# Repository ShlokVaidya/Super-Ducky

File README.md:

# Super-Ducky
# RP2350A Dual-Mode USB Device

## 1. Description

This project is a custom USB storage and control device powered by the **Raspberry Pi RP2350A** microcontroller. It serves as a dualmode device separating system firmware from user data through a high-speed eMMC interface

The system architecture utilizes a 4-layer PCB to maintain signal integrity for high-speed digital lines (USB and eMMC).

| Component | Function |
| :---- | :---- |
| **RP2350A** | Central MCU handling USB stack and storage logic |
| **eMMC (16GB)** | High density mass storage for user data |
| **QSPI Flash** | Dedicated firmware and bootloader execution |
| **LDO Regulators** | AP2112K series for stable 1.8V and 3.3V rails |
| **USB Mux** | TS3USB221 for signal routing and integrity |

## 2. Why I Built This

I built this project to explore **full stack embedded system development**.

Most beginner projects focus only on firmware or simple microcontroller boards. This project instead focuses on the **entire engineering process** including:

- **Hardware Architecture:** Designing a system that separates firmware execution (QSPI) from high-capacity storage (eMMC).
- **Advanced Sourcing:** Navigating global supply chains to source specialized ICs like the MTFC16GAKAEDQ-AIT eMMC via JLCPCB Global Sourcing.
- **High-Speed Design:** Learning to route differential USB pairs and high-clock-rate storage interfaces on a multi-layer board.
- **Power Management:** Implementing a multi-rail (3.3V/1.8V) system to satisfy different logic level requirements.

The goal was to move beyond hobbyist "breadboarding" and understand how professional-grade embedded products are engineered from the ground up.

## 3. How to Use the Device

1. **Connection:** Connect the device to a computer using a standard USB-C cable.
2. **Standard Operation:** The RP2350A initializes, loads firmware from the QSPI flash, and mounts the eMMC as a storage drive or serial device depending on the firmware configuration.
3. **Boot Selection:** To update firmware or change modes, hold the **Boot Button (GPIO22)** while plugging in the device. This forces the RP2350A into its native USB bootloader mode.
4. **Data Access:** Once connected, the host computer interacts with the 16GB eMMC through the high-speed USB interface managed by the MCU.

## 4. Hardware Visualization

### Full Schematic

### PCB Layout

### 3D Render

### BOM

## 5. Bill of Materials (BOM)

The following table lists all 20 parts required for the assembly, consolidated from the design files and JLCPCB procurement logs.

| Parts Type | JLCPCB Part \# | MFR Part \# | Link | Description | Unit Price | Qty | Total Price |
| :---- | :---- | :---- | :---- | :---- | :---- | :---- | :---- |
| stock | C1711 | CL21B104KBCNNNC | https://jlcpcb.com/partdetail/2063-CL21B104KBCNNNC/C1711 | 100nF 50V X7R ±10% 0805 Multilayer Ceramic Capacitors MLCC \- SMD/SMT ROHS | 0.0062 | 16 | 0.1 |
| stock | C8429 | WJ2EDGV-5.08-04P-14-00A | https://jlcpcb.com/partdetail/8923-WJ2EDGV\_5\_08\_04P\_1400A/C8429 | \-40℃\~+105℃ 1 10A 1x4P 300V 4 4P 5.08mm Board Side/Socket \- Open Green Hinged (Snap On) Through Hole Plugin,P=5.08mm Pluggable System Terminal Block ROHS | 0.0905 | 2 | 0.19 |
| stock | C1779 | CL21A475KAQNNNE | https://jlcpcb.com/partdetail/2131-CL21A475KAQNNNE/C1779 | 25V 4.7uF X5R ±10% 0805 Multilayer Ceramic Capacitors MLCC \- SMD/SMT ROHS | 0.0143 | 2 | 0.03 |
| buy | C6006988 | UP31-CV-G-CM | https://jlcpcb.com/partdetail/CUI-UP31\_CV\_GCM/C6006988 | \- USB Connectors ROHS | 2.265 | 4 | 9.06 |
| stock | C71617 | CRCW040210K0FKED | https://jlcpcb.com/partdetail/VishayIntertech-CRCW040210K0FKED/C71617 | \-55℃\~+155℃ 10kΩ 50V 63mW Thick Film Resistor ±1% ±100ppm/℃ 0402 Chip Resistor \- Surface Mount ROHS | 0.0035 | 6 | 0.03 |
| buy | C100612 | CR0402JF0220G | https://jlcpcb.com/partdetail/LIZElec-CR0402JF0220G/C100612 | \-55℃\~+125℃ 22Ω 50V 62.5mW Thick Film Resistor ±200ppm/℃ ±5% 0402 Chip Resistor \- Surface Mount ROHS | 0.0003 | 10000 | 3 |
| stock | C25905 | 0402WGF5101TCE | https://jlcpcb.com/partdetail/26648-0402WGF5101TCE/C25905 | \-55℃\~+155℃ 5.1kΩ 50V 62.5mW Thick Film Resistor ±1% ±100ppm/℃ 0402 Chip Resistor \- Surface Mount ROHS | 0.0008 | 4 | 0.01 |
| stock | C25792 | 0402WGF4702TCE | https://jlcpcb.com/partdetail/26535-0402WGF4702TCE/C25792 | \-55℃\~+155℃ 47kΩ 50V 62.5mW Thick Film Resistor ±1% ±100ppm/℃ 0402 Chip Resistor \- Surface Mount ROHS | 0.0008 | 10 | 0.01 |
| stock | C25530 | 0402WGJ0104TCE | https://jlcpcb.com/partdetail/26273-0402WGJ0104TCE/C25530 | \-55℃\~+155℃ 100kΩ 50V 62.5mW Thick Film Resistor ±100ppm/℃ ±5% 0402 Chip Resistor \- Surface Mount ROHS | 0.0006 | 4 | 0.01 |
| stock | C25076 | 0402WGF1000TCE | https://jlcpcb.com/partdetail/25819-0402WGF1000TCE/C25076 | \-55℃\~+155℃ 100Ω 50V 62.5mW Thick Film Resistor ±1% ±100ppm/℃ 0402 Chip Resistor \- Surface Mount ROHS | 0.0008 | 2 | 0.01 |
| stock | C1712 | CL21B105KAFNFNE | https://jlcpcb.com/partdetail/2064-CL21B105KAFNFNE/C1712 | 1uF 25V X7R ±10% 0805 Multilayer Ceramic Capacitors MLCC \- SMD/SMT ROHS | 0.0133 | 18 | 0.24 |
| stock | C138714 | TPD4E05U06DQAR | https://jlcpcb.com/partdetail/TexasInstruments-TPD4E05U06DQAR/C138714 | \-40℃\~+125℃ 0.5pF 10nA 14V 2.5A@8/20us 4 40W@8/20us 5.5V 6.5V ESD IEC 61000-4-2、IEC 61000-4-5、IEC 61000-4-4 Unidirectional USON-10(1x2.5) ESD and Surge Protection (TVS/ESD) ROHS | 0.072 | 2 | 0.15 |
| stock | C295091 | XJHCELNANF-12MHZ | https://jlcpcb.com/partdetail/TAITIENElec-XJHCELNANF12MHZ/C295091 | \-40℃\~+85℃ 12MHz 20pF Crystal Oscillator ±30ppm ±30ppm HC-49S-SMD Crystals ROHS | 0.1385 | 2 | 0.28 |
| stock | C176944 | AP2112K-1.8TRG1 | https://jlcpcb.com/partdetail/DiodesIncorporated-AP2112K\_18TRG1/C176944 | \-40℃\~+85℃@(Ta) 1 1.8V 500mV@(600mA) 50uVrms 55uA 600mA 65dB@(1kHz) 6V Fixed Over Current Protection、Over Temperature Protection、Enable Positive SOT-25 Voltage Regulators \- Linear, Low Drop Out (LDO) Regulators ROHS | 0.1103 | 2 | 0.23 |
| stock | C128396 | TS3USB221ARSER | https://jlcpcb.com/partdetail/TexasInstruments-TS3USB221ARSER/C128396 | \-40℃\~+85℃ 12ns 2.3V\~3.6V 250ps 2:1 30ns 6pF 6Ω 900MHz USB UQFN-10(1.5x2) Analog Switches \- Special Purpose ROHS | 0.2515 | 2 | 0.51 |
| stock | C79167 | EVQP7A01P | https://jlcpcb.com/partdetail/PANASONIC-EVQP7A01P/C79167 | \-20℃\~+70℃ 1.35mm 100,000 cycles 12V 2.2N 3.55mm 3.5mm 50mA PC Pin Rectangular Button SPST Surface Mount, Right Angle SMD,3.6x3.5mm Tactile Switches ROHS | 0.1539 | 2 | 0.31 |
| stock | C42411118 | RP2350A | https://jlcpcb.com/partdetail/RaspberryPi-RP2350A/C42411118 | QFN-60-EP Microcontrollers (MCU/MPU/SOC) ROHS | 1.2406 | 2 | 2.49 |
| stock | C2613930 | W25Q128JVSIM | https://jlcpcb.com/partdetail/WinbondElec-W25Q128JVSIM/C2613930 | \-40℃\~+85℃ 100,000 cycles 10uA 128Mbit 133MHz 150ms@(64KB) 2.7V\~3.6V 20 Years 400us SPI SOIC-8-208mil NOR FLASH ROHS | 3.2212 | 2 | 6.45 |
| stock | C23380830 | AP2112K-3.3TRG1 | https://jlcpcb.com/partdetail/TECHPUBLIC-AP2112K\_33TRG1/C23380830 | \-40℃\~+85℃@(Ta) 1 10uA 3.3V 320mV@(600mA) 5.5V 600mA 75dB@(1kHz) Fixed Over Temperature Protection Positive SOT-23-5 Voltage Regulators \- Linear, Low Drop Out (LDO) Regulators ROHS | 0.1029 | 2 | 0.21 |

| Parts Type | JLCPCB Part \# | Digikey-ID | MFR Part \# | Description | Unit Price | Qty | Total Price |
| :---- | :---- | :---- | :---- | :---- | :---- | :---- | :---- |
| overseas\_shop | C30839157 | digikey \#: 557-1967-1-ND | MTFC16GAKAEDQ-AIT TR | IC FLASH 128GBIT MMC 100LBGA | 41.6132 | 2 | 83.23 |
***

## 6. Billing Summary

Total expenditure for PCB fabrication, assembly, and parts based on project records.

| Category | Cost (INR) | Cost (USD) |
| :---- | :---- | :---- |
| **JLCPCB Assembly (PCBA)** | ₹6,621.82 | $72.84 |
| **Component Sourcing (Global \+ Stock)** | ₹9686.36 | $106.55 |
| **Grand Total** | **₹16308.18** | **$179.39** |

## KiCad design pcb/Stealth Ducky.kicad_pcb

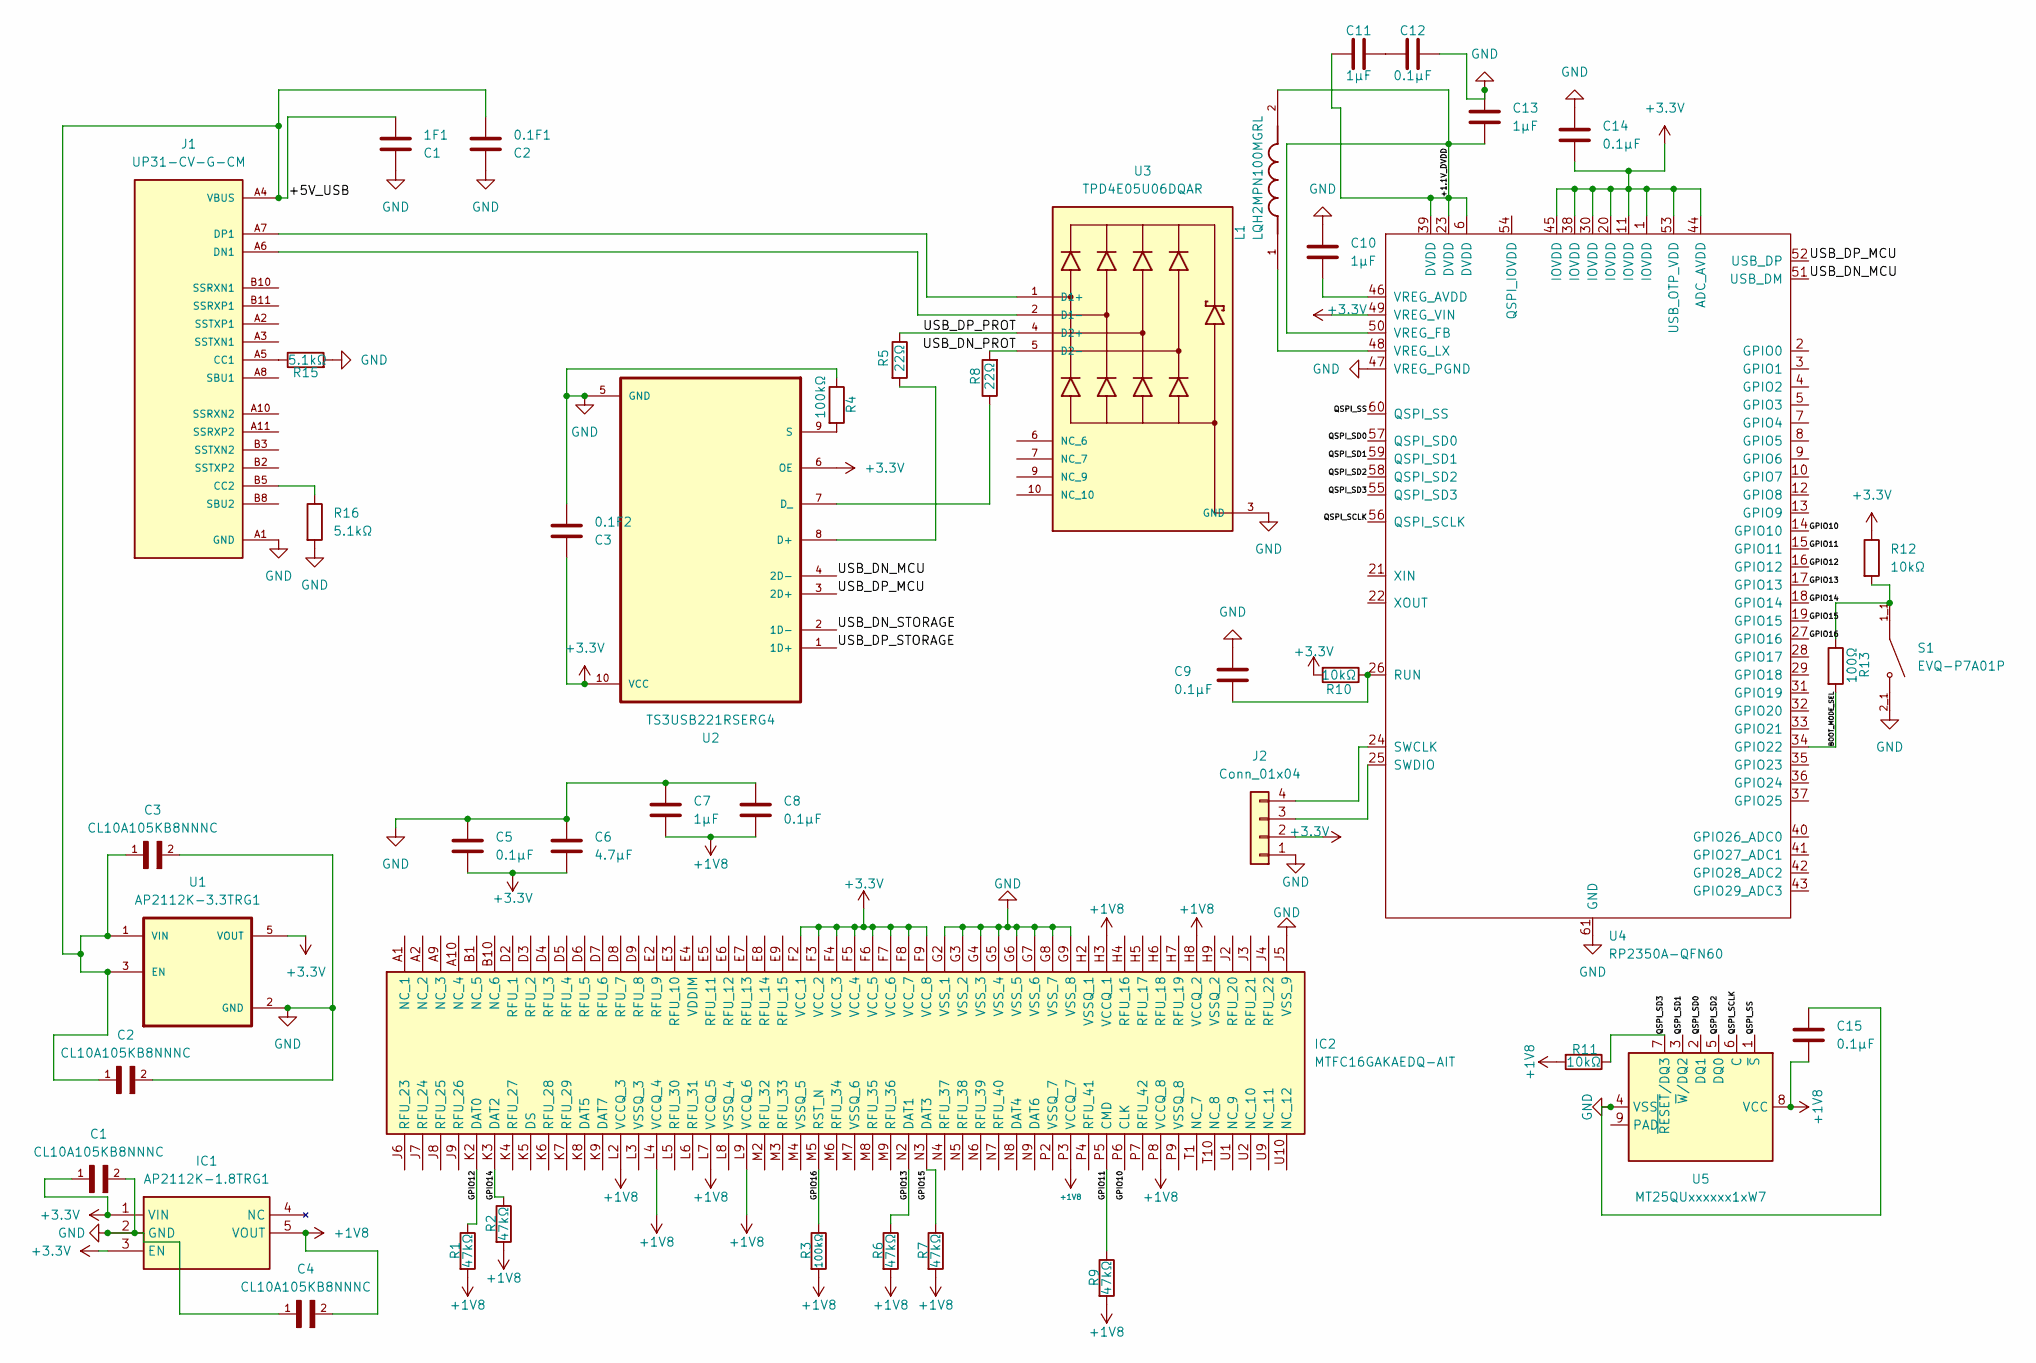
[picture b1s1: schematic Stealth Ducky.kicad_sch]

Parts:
0.1F1: C2; C_0805_2012Metric_Pad1.18x1.45mm_HandSolder
0.1F2: C3; C_0805_2012Metric_Pad1.18x1.45mm_HandSolder
1F1: C1; C_0805_2012Metric_Pad1.18x1.45mm_HandSolder
C1, C2, C3, C4: CL10A105KB8NNNC; C_0805_2012Metric_Pad1.18x1.45mm_HandSolder
C5, C8, C9, C12, C14, C15: 0.1µF; C_0805_2012Metric_Pad1.18x1.45mm_HandSolder
C6: 4.7µF; C_0805_2012Metric_Pad1.18x1.45mm_HandSolder
C7, C10, C11, C13: 1µF; C_0805_2012Metric_Pad1.18x1.45mm_HandSolder
IC1: AP2112K-1.8TRG1; SOT95P285X140-5N; Manufacturer_Part_Number AP2112K-1.8TRG1; Mouser Part Number 621-AP2112K-1.8TRG1
IC2: MTFC16GAKAEDQ-AIT; BGA100C100P10X17_1400X1800X140; Manufacturer_Part_Number MTFC16GAKAEDQ-AIT; Mouser Part Number 340-274027-TRAY
J1: UP31-CV-G-CM; CUI_UP31-CV-G-CM; PARTREV 1.04
J2: Conn_01x04; Samtec_HPM-04-01-x-S_Straight_1x04_Pitch5.08mm
L1: LQH2MPN100MGRL; IND_LQH2MPN100MGRL; PARTREV N/A
R1, R2, R6, R7, R9: 47kΩ; R_0402_1005Metric
R3, R4: 100kΩ; R_0402_1005Metric
R5, R8: 22Ω; R_0402_1005Metric
R10, R11, R12: 10kΩ; R_0402_1005Metric
R13: 100Ω; R_0402_1005Metric
R15, R16: 5.1kΩ; R_0402_1005Metric
S1: EVQ-P7A01P; SW_EVQ-P7A01P; PARTREV 2022.4
U1: AP2112K-3.3TRG1; SOT95P285X140-5N (2); PARTREV 2-2
U2: TS3USB221RSERG4; IC_TPD6E001RSER
U3: TPD4E05U06DQAR; IC_TPD4E05U06DQAR; PARTREV N
U4: RP2350A-QFN60; RP2350A_QFN-60_EP_7.75x7.75_Pitch0.4mm
U5: MT25QUxxxxxx1xW7; W-PDFN-8-1EP_6x5mm_P1.27mm_EP3x3mm

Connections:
+1V8: C4.2, C7.1, C8.1, C15.1, IC1.5 (VOUT), IC2.H3 (VCCQ_1), IC2.H8 (VCCQ_2), IC2.L2 (VCCQ_3), IC2.L4 (VCCQ_4), IC2.L7 (VCCQ_5), IC2.L9 (VCCQ_6), IC2.P3 (VCCQ_7), IC2.P8 (VCCQ_8), R1.2, R2.2, R3.2, R6.2, R7.2, R9.2, R11.2, U5.8 (VCC)
+3.3V: 0.1F2.1, C1.1, C5.1, C6.1, C14.2, IC1.1 (VIN), IC1.3 (EN), IC2.F2 (VCC_1), IC2.F3 (VCC_2), IC2.F4 (VCC_3), IC2.F5 (VCC_4), IC2.F6 (VCC_5), IC2.F7 (VCC_6), IC2.F8 (VCC_7), IC2.F9 (VCC_8), J2.2, R10.2, R12.1, U1.5 (VOUT), U2.6 (OE), U2.10 (VCC), U4.1 (IOVDD), U4.11 (IOVDD), U4.20 (IOVDD), U4.30 (IOVDD), U4.38 (IOVDD), U4.44 (ADC_AVDD), U4.45 (IOVDD), U4.49 (VREG_VIN), U4.53 (USB_OTP_VDD)
/+1.1V_DVDD: C11.2, C13.2, L1.2, U4.6 (DVDD), U4.23 (DVDD), U4.39 (DVDD), U4.50 (VREG_FB)
/BOOT_MODE_SEL: R13.2, U4.34 (GPIO22)
/GPIO10: IC2.P6 (CLK), U4.14 (GPIO10)
/GPIO11: IC2.P5 (CMD), R9.1, U4.15 (GPIO11)
/GPIO12: IC2.K2 (DAT0), R1.1, U4.16 (GPIO12)
/GPIO13: IC2.N2 (DAT1), R6.1, U4.17 (GPIO13)
/GPIO14: IC2.K3 (DAT2), R2.1, U4.18 (GPIO14)
/GPIO15: IC2.N3 (DAT3), R7.1, U4.19 (GPIO15)
/GPIO16: IC2.M5 (RST_N), R3.1, U4.27 (GPIO16)
/QSPI_SCLK: U4.56 (QSPI_SCLK), U5.6 (C)
/QSPI_SD0: U4.57 (QSPI_SD0), U5.2 (DQ1)
/QSPI_SD1: U4.59 (QSPI_SD1), U5.3 (~W/DQ2)
/QSPI_SD2: U4.58 (QSPI_SD2), U5.5 (DQ0)
/QSPI_SD3: R11.1, U4.55 (QSPI_SD3), U5.7 (~RESET/DQ3)
/QSPI_SS: U4.60 (QSPI_SS), U5.1 (~S)
/USB_DN_MCU: U2.4 (2D-), U4.51 (USB_DM)
/USB_DN_PROT: R8.2, U3.5 (D2-)
/USB_DN_STORAGE: U2.2 (1D-)
/USB_DP_MCU: U2.3 (2D+), U4.52 (USB_DP)
/USB_DP_PROT: R5.1, U3.4 (D2+)
/USB_DP_STORAGE: U2.1 (1D+)
GND: 0.1F1.2, 0.1F2.2, 1F1.2, C1.2, C2.2, C3.2, C4.1, C5.2, C6.2, C7.2, C8.2, C9.1, C10.1, C12.1, C13.1, C14.1, C15.2, IC1.2 (GND), IC2.G2 (VSS_1), IC2.G3 (VSS_2), IC2.G4 (VSS_3), IC2.G5 (VSS_4), IC2.G6 (VSS_5), IC2.G7 (VSS_6), IC2.G8 (VSS_7), IC2.G9 (VSS_8), IC2.J5 (VSS_9), J1.A1 (GND), J1.A12 (GND), J1.B1 (GND), J1.B12 (GND), J2.1, R4.1, R15.2, R16.2, S1.2_1, S1.2_2, U1.2 (GND), U2.5 (GND), U3.3 (GND), U3.8 (GND), U4.47 (VREG_PGND), U4.61 (GND), U5.4 (VSS)
unnamed: C11.1, C12.2
unnamed: J1.A5 (CC1), R15.1
unnamed: J1.B5 (CC2), R16.1
unnamed: J1.A6 (DN1), U3.2 (D1-)
unnamed: J1.A7 (DP1), U3.1 (D1+)
unnamed: J2.3, U4.25 (SWDIO)
unnamed: J2.4, U4.24 (SWCLK)
unnamed: R12.2, R13.1, S1.1_1, S1.1_2
unnamed: R5.2, U2.8 (D+)
unnamed: R8.1, U2.7 (D_)
unnamed: R4.2, U2.9 (S)
unnamed: C9.2, R10.1, U4.26 (RUN)
unnamed: C10.2, U4.46 (VREG_AVDD)
unnamed: L1.1, U4.48 (VREG_LX)
VBUS: 0.1F1.1, 1F1.1, C2.1, C3.1, J1.A4 (VBUS), J1.A9 (VBUS), J1.B4 (VBUS), J1.B9 (VBUS), U1.1 (VIN), U1.3 (EN)

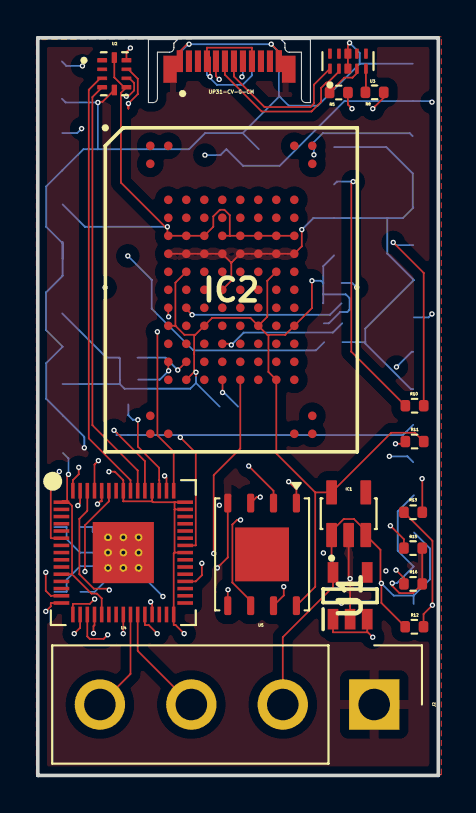
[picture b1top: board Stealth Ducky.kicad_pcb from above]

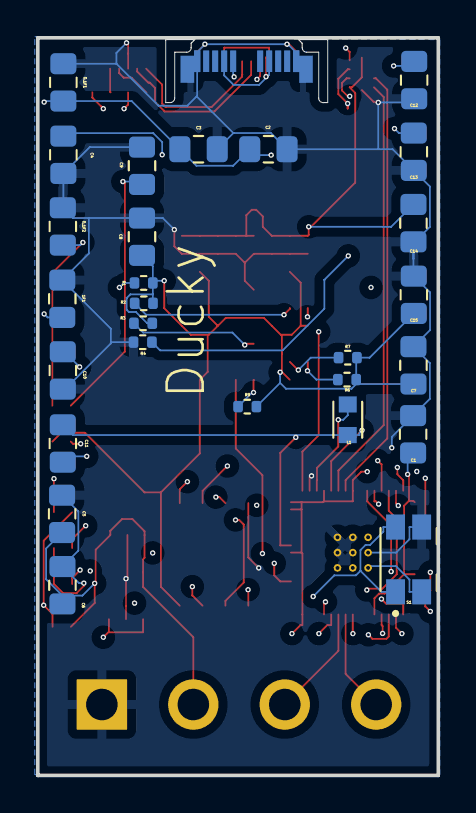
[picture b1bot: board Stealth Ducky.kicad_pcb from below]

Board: 4 copper layers, 22.2 x 41.0 mm, 44 parts (27 on the bottom side), 37 nets.

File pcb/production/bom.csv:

Designator,Footprint,Quantity,Value,LCSC Part #,
0.1F1,0805,1,C2,,5
0.1F2,0805,1,C3,,5
1F1,0805,1,C1,,5
"C1, C2, C3, C4",0805,4,CL10A105KB8NNNC,,20
"C10, C11, C13, C7",0805,4,1µF,,20
"C12, C14, C15, C5, C8, C9",0805,6,0.1µF,,30
C6,0805,1,4.7µF,,5
IC1,SOT95P285X140-5N,1,AP2112K-1.8TRG1,,2
IC2,BGA100C100P10X17_1400X1800X140,1,MTFC16GAKAEDQ-AIT,,2
J1,CUI_UP31-CV-G-CM,1,UP31-CV-G-CM,,2
J2,Samtec_HPM-04-01-x-S_Straight_1x04_Pitch5.08mm,1,Conn_01x04,,2
L1,IND_LQH2MPN100MGRL,1,LQH2MPN100MGRL,,2
"R1, R2, R6, R7, R9",0402,5,47kΩ,,10
"R10, R11, R12",0402,3,10kΩ,,6
R13,0402,1,100Ω,,2
"R15, R16",0402,2,5.1kΩ,,4
"R3, R4",0402,2,100kΩ,,4
"R5, R8",0402,2,22Ω,,4
S1,SW_EVQ-P7A01P,1,EVQ-P7A01P,,2
U1,SOT95P285X140-5N (2),1,AP2112K-3.3TRG1,,2
U2,IC_TPD6E001RSER,1,TS3USB221RSERG4,,2
U3,IC_TPD4E05U06DQAR,1,TPD4E05U06DQAR,,2
U4,RP2350A_QFN-60_EP_7.75x7.75_Pitch0.4mm,1,RP2350A-QFN60,,2
U5,W-PDFN-8-1EP_6x5mm_P1.27mm_EP3x3mm,1,MT25QUxxxxxx1xW7,,2

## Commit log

2026-03-05 v2.1
2026-03-05 grammer correction
